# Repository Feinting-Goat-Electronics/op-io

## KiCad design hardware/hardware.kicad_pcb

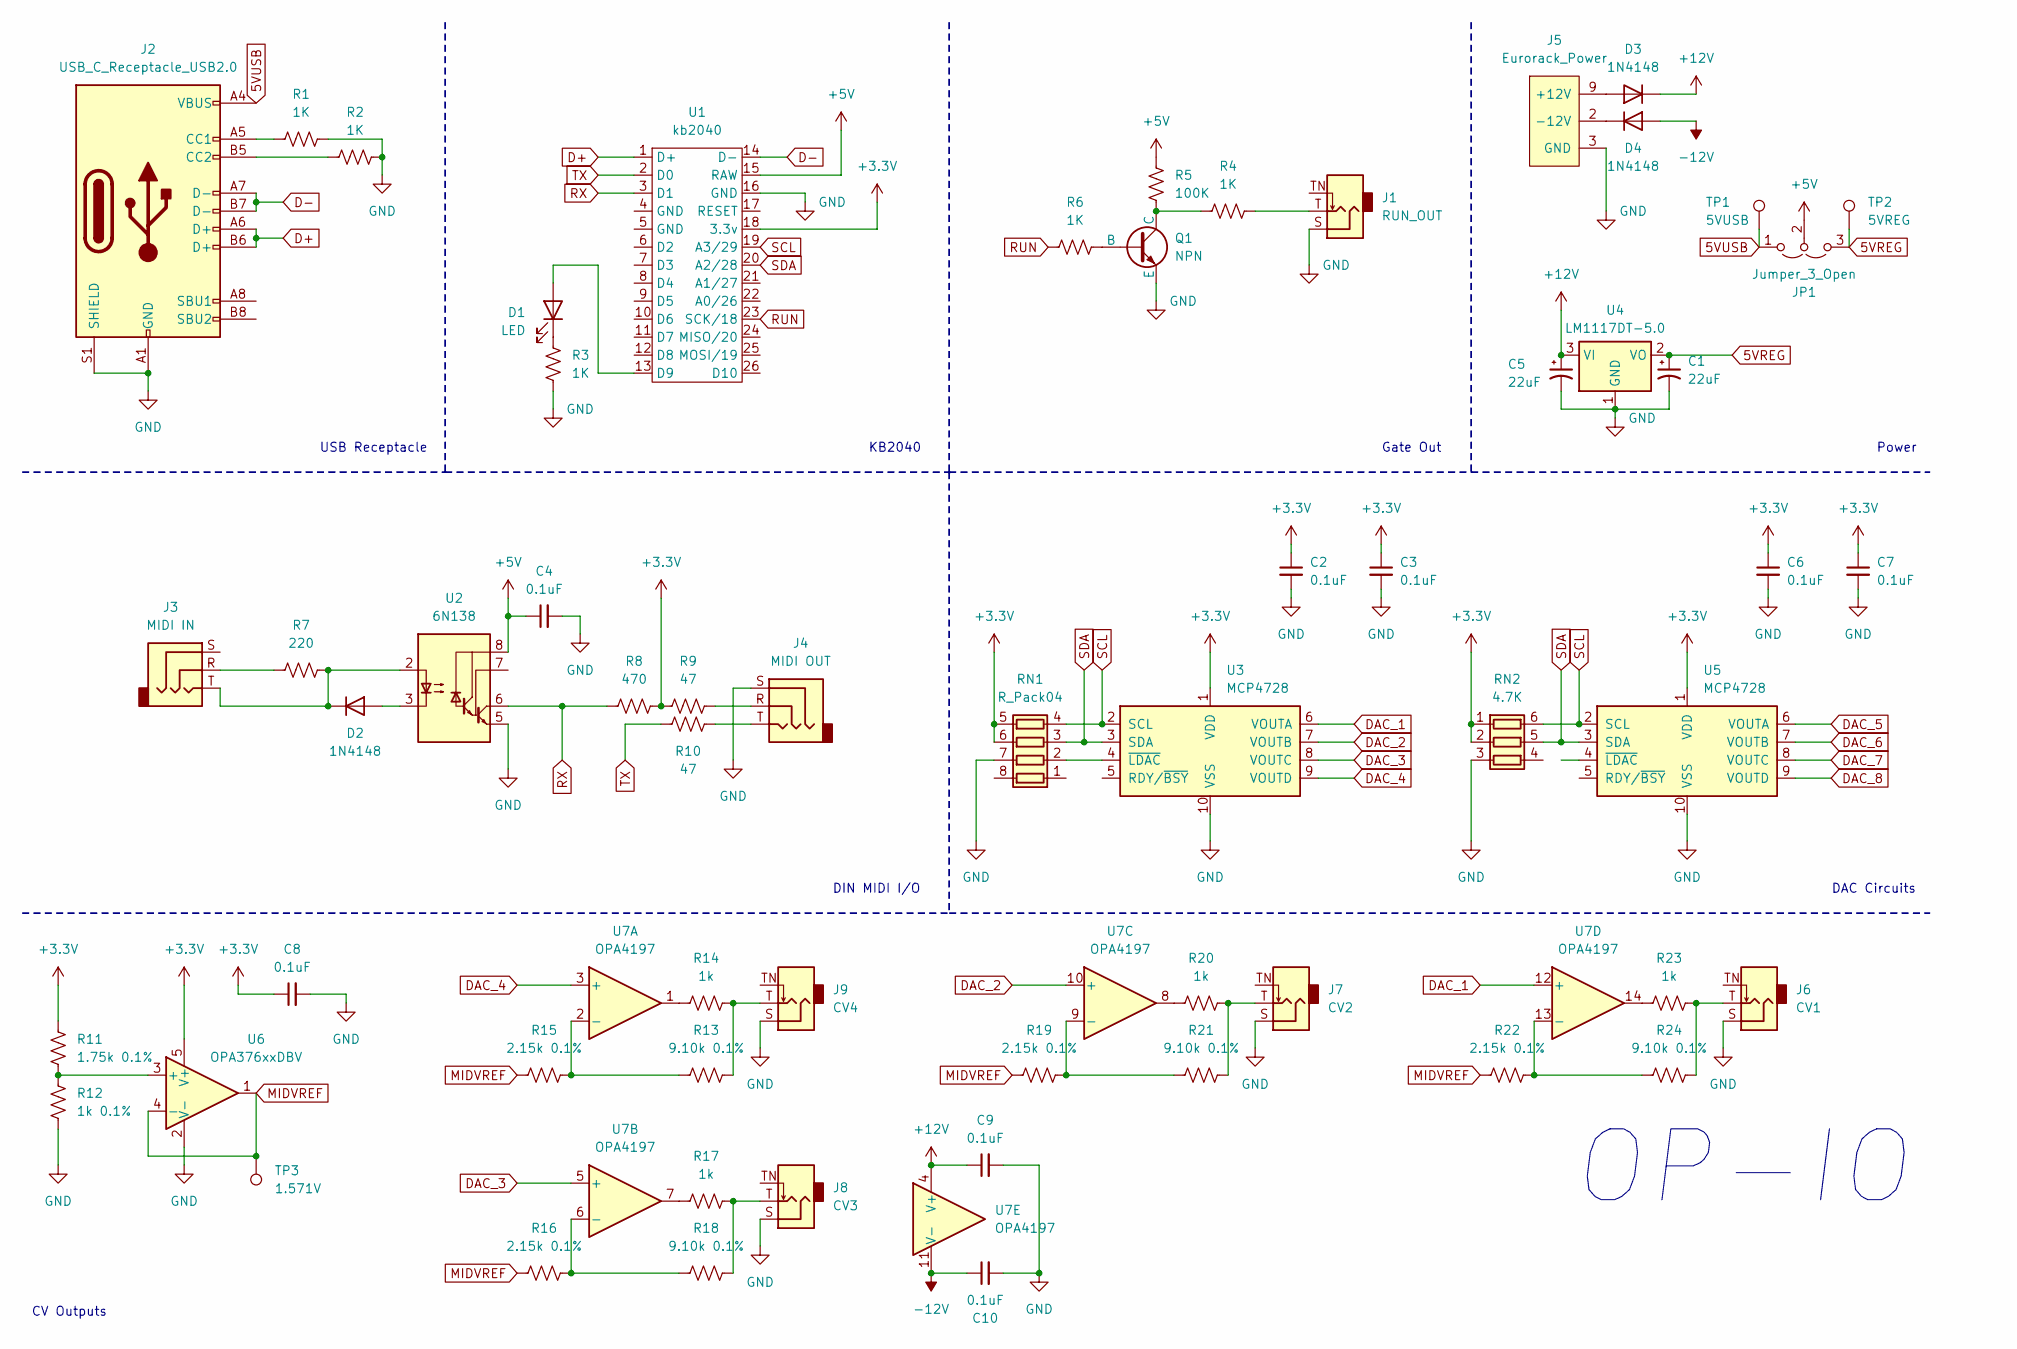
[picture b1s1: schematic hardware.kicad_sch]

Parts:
C1, C5: 22uF; CP_Elec_6.3x7.7
C2, C3, C4, C6, C7, C8, C9, C10: 0.1uF; C_0805_2012Metric
D1: LED; LED_D3.0mm_FlatTop
D2, D3, D4: 1N4148; D_SOD-123
J1: RUN_OUT; AudioJack_WQP518MA; MPN WQP-WQP518MA
J2: USB_C_Receptacle_USB2.0; USB_C_Receptacle_GCT_USB4115-03-C
J3: MIDI IN; Jack_3.5mm_QingPu_WQP-PJ366ST_Vertical
J4: MIDI OUT; Jack_3.5mm_QingPu_WQP-PJ366ST_Vertical
J5: Eurorack_Power; Eurorack_Power_2x5_Shrouded; MPN 302-S101
J6: CV1; AudioJack_WQP518MA; MPN WQP-WQP518MA
J7: CV2; AudioJack_WQP518MA; MPN WQP-WQP518MA
J8: CV3; AudioJack_WQP518MA; MPN WQP-WQP518MA
J9: CV4; AudioJack_WQP518MA; MPN WQP-WQP518MA
JP1: Jumper_3_Open; SolderJumper-3_P1.3mm_Open_Pad1.0x1.5mm
Q1: NPN; SOT-23-3
R1, R2, R3, R4, R6: 1K; R_0805_HandSolder
R5: 100K; R_0805_HandSolder
R7: 220; R_0805_HandSolder
R8: 470; R_0805_HandSolder
R9, R10: 47; R_0805_HandSolder
R11: 1.75k 0.1%; R_0805_HandSolder
R12: 1k 0.1%; R_0805_HandSolder
R13, R18, R21, R24: 9.10k 0.1%; R_0805_HandSolder
R14, R17, R20, R23: 1k; R_0805_HandSolder
R15, R16, R19, R22: 2.15k 0.1%; R_0805_HandSolder
RN1: R_Pack04; R_Array_Convex_4x0612
RN2: 4.7K; R_Array_Convex_4x1206
TP1: 5VUSB; TestPoint_Pad_D2.5mm
TP2: 5VREG; TestPoint_Pad_D2.5mm
TP3: 1.571V; TestPoint_Pad_D2.5mm
U1: kb2040
U2: 6N138; SMDIP-8_W9.53mm
U3, U5: MCP4728; MSOP-10_3x3mm_P0.5mm
U4: LM1117DT-5.0; TO-252-3_TabPin2
U6: OPA376xxDBV; SOT-23-5
U7: OPA4197; TSSOP-14_4.4x5mm_P0.65mm; MPN OPA4197IPW

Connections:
5VREG: C1.1, JP1.3 (B), TP2.1, U4.2 (VO)
5VUSB: J2.A4 (VBUS), J2.A9 (VBUS), J2.B4 (VBUS), J2.B9 (VBUS), JP1.1 (A), TP1.1
+3.3V: C2.1, C3.1, C6.1, C7.1, C8.1, R8.1, R9.2, R11.1, RN1.5 (R4.2), RN1.6 (R3.2), RN2.1 (R1.1), RN2.2 (R2.1), U1.18 (3.3v), U3.1 (VDD), U5.1 (VDD), U6.5 (V+)
+5V: C4.1, JP1.2 (C), R5.2, U1.15 (RAW), U2.8 (VCC)
+12V: C5.1, C9.1, D3.1 (K), U4.3 (VI), U7.4 (V+)
-12V: C10.1, D4.2 (A), U7.11 (V-)
D+: J2.A6 (D+), J2.B6 (D+), U1.1 (D+)
D-: J2.A7 (D-), J2.B7 (D-), U1.14 (D-)
DAC_1: U3.6 (VOUTA), U7.12 (+)
DAC_2: U3.7 (VOUTB), U7.10 (+)
DAC_3: U3.8 (VOUTC), U7.5 (+)
DAC_4: U3.9 (VOUTD), U7.3 (+)
GND: C1.2, C2.2, C3.2, C4.2, C5.2, C6.2, C7.2, C8.2, C9.2, C10.2, J1.S (Sleeve), J2.A1 (GND), J2.A12 (GND), J2.B1 (GND), J2.B12 (GND), J2.S1 (SHIELD), J4.S, J5.3 (GND), J5.4 (GND), J5.5 (GND), J5.6 (GND), J5.7 (GND), J5.8 (GND), J6.S (Sleeve), J7.S (Sleeve), J8.S (Sleeve), J9.S (Sleeve), Q1.3 (E), R1.2, R2.2, R3.1, R12.2, RN1.7 (R2.2), RN2.3 (R3.1), U1.16 (GND), U2.5 (GND), U3.10 (VSS), U4.1 (GND), U5.10 (VSS), U6.2 (V-)
MIDVREF: R15.1, R16.1, R19.1, R22.1, TP3.1, U6.1, U6.4 (-)
unnamed: D1.2 (A), U1.13 (D9)
unnamed: D1.1 (K), R3.2
unnamed: D2.2 (A), U2.3 (C2)
unnamed: D2.1 (K), J3.T, R7.1, U2.2 (C1)
unnamed: D3.2 (A), J5.9 (+12V), J5.10 (+12V)
unnamed: D4.1 (K), J5.1 (-12V), J5.2 (-12V)
unnamed: J1.T (Tip), R4.2
unnamed: J2.A5 (CC1), R1.1
unnamed: J2.B5 (CC2), R2.1
unnamed: J3.R, R7.2
unnamed: J4.R, R9.1
unnamed: J4.T, R10.2
unnamed: J6.T (Tip), R23.2, R24.2
unnamed: J7.T (Tip), R20.2, R21.2
unnamed: J8.T (Tip), R17.2, R18.2
unnamed: J9.T (Tip), R13.2, R14.2
unnamed: Q1.2 (B), R6.2
unnamed: Q1.1 (C), R4.1, R5.1
unnamed: R14.1, U7.1
unnamed: R17.1, U7.7
unnamed: R20.1, U7.8
unnamed: R23.1, U7.14
unnamed: RN1.2 (R2.1), U3.4 (~LDAC)
unnamed: R11.2, R12.1, U6.3 (+)
unnamed: R13.1, R15.2, U7.2 (-)
unnamed: R16.2, R18.1, U7.6 (-)
unnamed: R19.2, R21.1, U7.9 (-)
unnamed: R22.2, R24.1, U7.13 (-)
RUN: R6.1, U1.23 (SCK/18)
RX: R8.2, U1.3 (D1), U2.6 (VO2)
SCL: RN1.4 (R4.1), RN2.6 (R1.2), U1.19 (A3/29), U3.2 (SCL), U5.2 (SCL)
SDA: RN1.3 (R3.1), RN2.5 (R2.2), U1.20 (A2/28), U3.3 (SDA), U5.3 (SDA)
TX: R10.1, U1.2 (D0)

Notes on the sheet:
DIN MIDI I/O
KB2040
CV Outputs
Power
DAC Circuits
Gate Out
OP-IO
USB Receptacle

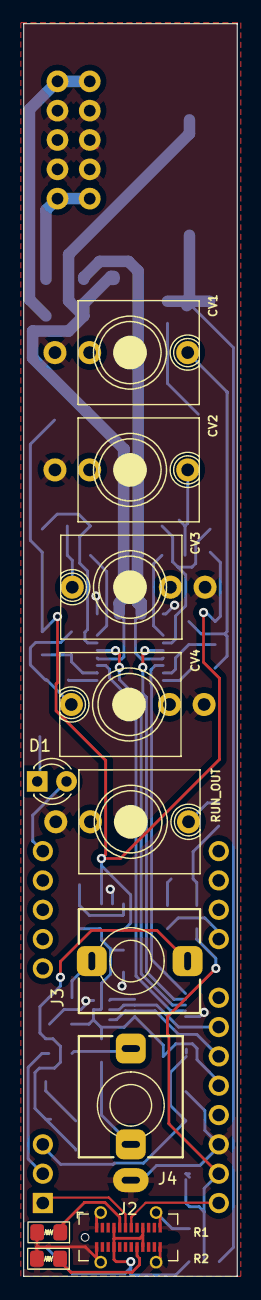
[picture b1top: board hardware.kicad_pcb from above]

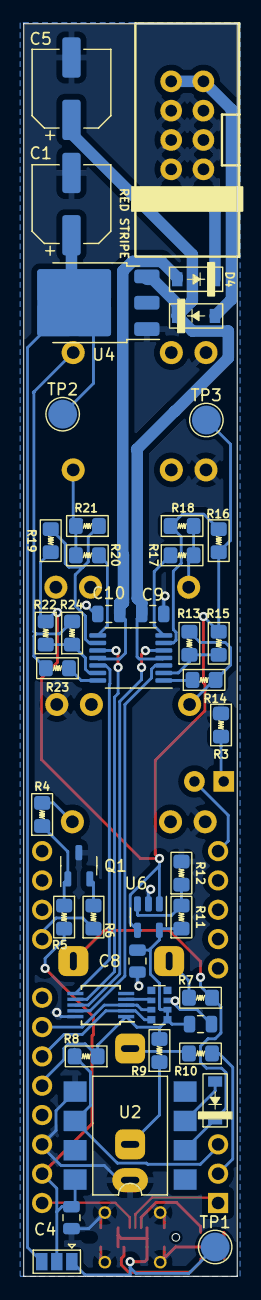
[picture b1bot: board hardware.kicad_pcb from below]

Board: 2 copper layers, 18.5 x 108.5 mm, 56 parts (45 on the bottom side), 47 nets.

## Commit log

2023-10-03 init
2024-01-01 added .gitignore
2024-01-01 updated gitignore
2024-01-01 finished initial PCB layout
2024-01-07 ready for fab
